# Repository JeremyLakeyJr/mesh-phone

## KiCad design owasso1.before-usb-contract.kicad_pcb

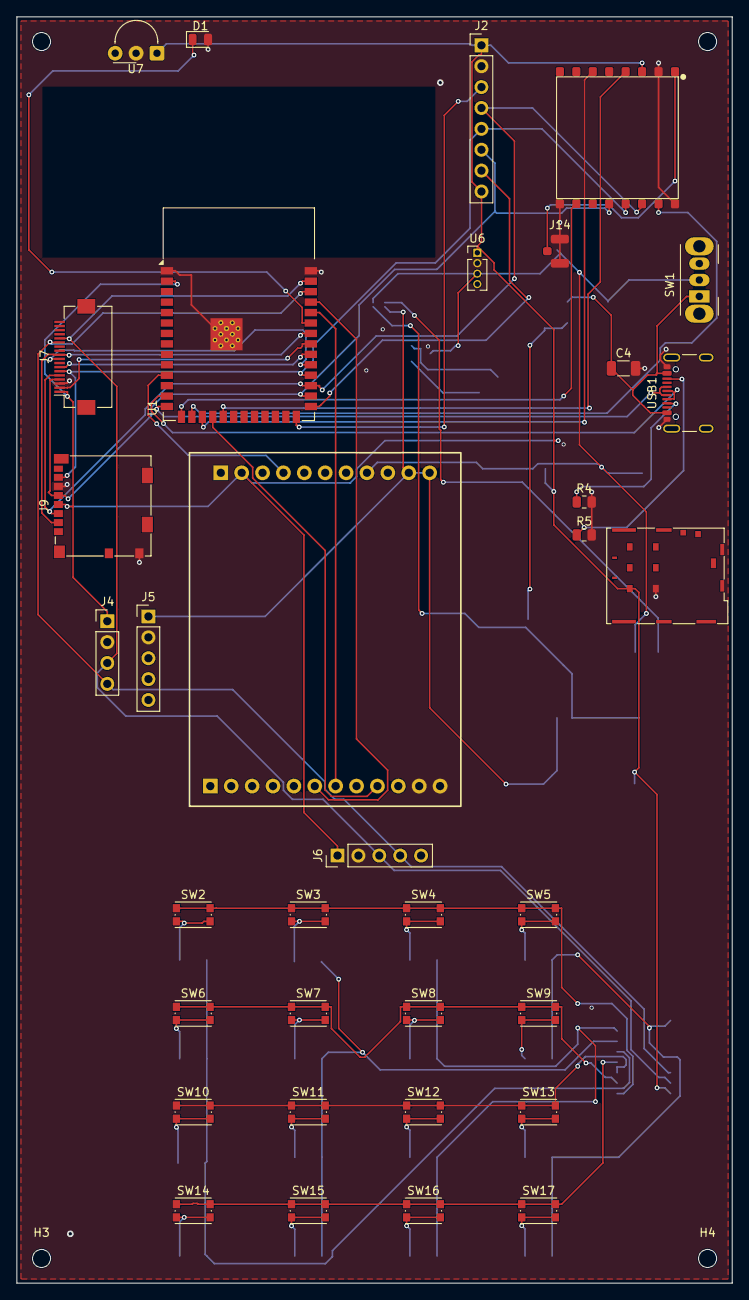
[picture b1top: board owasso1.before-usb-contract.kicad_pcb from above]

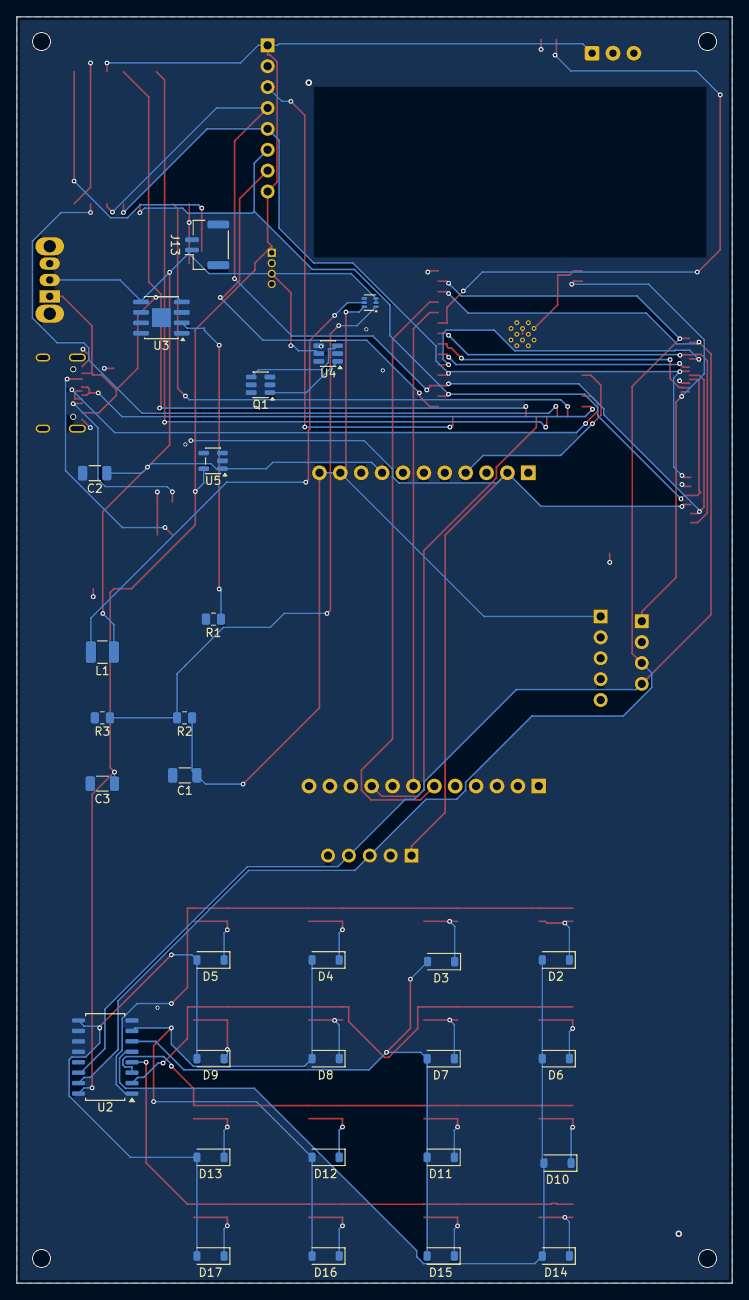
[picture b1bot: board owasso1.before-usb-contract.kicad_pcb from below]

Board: 2 copper layers, 87.0 x 154.0 mm, 69 parts (31 on the bottom side), 59 nets.

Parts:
C1: 1000uF-MODEM-BULK; C_1206_3216Metric
C2: 100uF-VBAT-BULK; C_1206_3216Metric
C3: 10uF-3V3-BULK; C_1206_3216Metric
C4: 10uF-USB-IN; C_1206_3216Metric
D1: TSAL6200-IR-LED; LED_0805_2012Metric
D2: 1N4148W-KEY-1; D_SOD-123
D3: 1N4148W-KEY-2; D_SOD-123
D4: 1N4148W-KEY-3; D_SOD-123
D5: 1N4148W-KEY-4; D_SOD-123
D6: 1N4148W-KEY-5; D_SOD-123
D7: 1N4148W-KEY-6; D_SOD-123
D8: 1N4148W-KEY-7; D_SOD-123
D9: 1N4148W-KEY-8; D_SOD-123
D10: 1N4148W-KEY-9; D_SOD-123
D11: 1N4148W-KEY-10; D_SOD-123
D12: 1N4148W-KEY-11; D_SOD-123
D13: 1N4148W-KEY-12; D_SOD-123
D14: 1N4148W-KEY-13; D_SOD-123
D15: 1N4148W-KEY-14; D_SOD-123
D16: 1N4148W-KEY-15; D_SOD-123
D17: 1N4148W-KEY-16; D_SOD-123
H1, H2, H3, H4: MountingHole_2.2mm_M2
J1: A7670E-LASE-23P-12+11; A7670E_LASE_23P_12+11
J2: CC1101-module; PinHeader_1x08_P2.54mm_Vertical
J3: Ra-01SH-SX1262-915MHz; Ra-01SH
J4: PN532-NFC-module; PinHeader_1x04_P2.54mm_Vertical
J5: RDM6300-RFID-module; PinHeader_1x05_P2.54mm_Vertical
J6: Pimoroni-PIM447-Trackball; PinHeader_1x05_P2.54mm_Vertical
J7: Waveshare-3.5in-18pin-FPC; Hirose_FH12-18S-0.5SH_1x18-1MP_P0.50mm_Horizontal
J9: MicroSD-SPI; microSD_HC_Molex_104031-0811
J10: Nano-SIM; JAE_SIM_Card_SF72S006
J13: LiPo-BATTERY-MICRO-JST-1.25; JST_GH_SM02B-GHS-TB_1x02-1MP_P1.25mm_Horizontal
J14: LoRa-UFL-Antenna; U.FL_Hirose_U.FL-R-SMT-1_Vertical
L1: 1uH-BOOST-INDUCTOR; L_1210_3225Metric
Q1: FS8205A-PROTECTION-FET; SOT-23-6
R1: 1.2k-TP4056-PROG; R_0805_2012Metric
R2: 180k-BOOST-FB; R_0805_2012Metric
R3: 27k-BOOST-FB; R_0805_2012Metric
R4: 5.1k-USB-C-CC1-Rd; R_0805_2012Metric
R5: 5.1k-USB-C-CC2-Rd; R_0805_2012Metric
SW1: Power-switch; SW_Slide_SPDT_Angled_CK_OS102011MA1Q
SW2: KEY-1; SW_Push_1P1T_NO_CK_KMR2
SW3: KEY-2; SW_Push_1P1T_NO_CK_KMR2
SW4: KEY-3; SW_Push_1P1T_NO_CK_KMR2
SW5: KEY-4; SW_Push_1P1T_NO_CK_KMR2
SW6: KEY-5; SW_Push_1P1T_NO_CK_KMR2
SW7: KEY-6; SW_Push_1P1T_NO_CK_KMR2
SW8: KEY-7; SW_Push_1P1T_NO_CK_KMR2
SW9: KEY-8; SW_Push_1P1T_NO_CK_KMR2
SW10: KEY-9; SW_Push_1P1T_NO_CK_KMR2
SW11: KEY-10; SW_Push_1P1T_NO_CK_KMR2
SW12: KEY-11; SW_Push_1P1T_NO_CK_KMR2
SW13: KEY-12; SW_Push_1P1T_NO_CK_KMR2
SW14: KEY-13; SW_Push_1P1T_NO_CK_KMR2
SW15: KEY-14; SW_Push_1P1T_NO_CK_KMR2
SW16: KEY-15; SW_Push_1P1T_NO_CK_KMR2
SW17: KEY-16; SW_Push_1P1T_NO_CK_KMR2
U1: ESP32-S3-WROOM-1-N16R8; ESP32-S3-WROOM-1
U2: PCF8574T-keypad-expander; SOIC-16_4.55x10.3mm_P1.27mm
U3: TP4056-charger; HSOP-8-1EP_3.9x4.9mm_P1.27mm_EP2.3x2.3mm
U4: DW01A-protection; SOT-23-6
U5: 3V3-LDO; SOT-23-5
U6: MAX17048-fuel-gauge; PinHeader_1x04_P1.27mm_Vertical
U7: TSOP38238-IR-receiver; Vishay_MINIMOLD-3Pin
U8: TPS61023DRLR-5V-BOOST; SOT-563
USB1: USB-C-charge-and-data; USB_C_Receptacle_GCT_USB4105-xx-A_16P_TopMnt_Horizontal

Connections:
/3V3: C3.1, J1.14, J2.1, J2.8, J3.3, J4.1, J6.1, J7.1, J9.4, J10.1, U1.2, U2.16, U5.5, U6.1, U7.1
/BOOST_FB: R2.2, R3.1, U8.1
/BOOST_SW: L1.2, U8.5
/CC1101_CS: J2.3, U1.26
/CC1101_GDO0: J2.7, U1.27
/DW01A_OC: Q1.4, U4.3
/DW01A_OD: Q1.1, U4.1
/GND: C1.2, C2.2, C3.2, C4.2, D1.2, J1.11, J1.12, J2.2, J3.2, J3.9, J3.16, J4.2, J5.2, J6.2, J7.3, J9.6, J9.10, J10.2, J13.2, J14.2, Q1.2, Q1.3, Q1.5, Q1.6, R1.2, R3.2, R4.2, R5.2, U1.1, U1.40, U1.41, U2.8, U2.10, U2.11, U2.12, U3.3, U3.9, U4.2, U4.4, U4.6, U5.2, U6.2, U7.2, U8.4, USB1.A1, USB1.A12, USB1.B1, USB1.B12
/I2C_SCL: J4.4, J6.4, J7.13, U1.38, U2.14
/I2C_SDA: J4.3, J6.3, J7.14, U1.39, U2.15
/IR_TX: D1.1, U1.35
/KEY_C1: D2.2, D6.2, D10.2, D14.2, U2.5
/KEY_C2: D3.2, D7.2, D11.2, D15.2, U2.6
/KEY_C3: D4.2, D8.2, D12.2, D16.2, U2.7
/KEY_C4: D5.2, D9.2, D13.2, D17.2, U2.9
/KEY_D1: D2.1, SW2.2
/KEY_D2: D3.1, SW3.2
/KEY_D3: D4.1, SW4.2
/KEY_D4: D5.1, SW5.2
/KEY_D5: D6.1, SW6.2
/KEY_D6: D7.1, SW7.2
/KEY_D7: D8.1, SW8.2
/KEY_D8: D9.1, SW9.2
/KEY_D9: D10.1, SW10.2
/KEY_D10: D11.1, SW11.2
/KEY_D11: D12.1, SW12.2
/KEY_D12: D13.1, SW13.2
/KEY_D13: D14.1, SW14.2
/KEY_D14: D15.1, SW15.2
/KEY_D15: D16.1, SW16.2
/KEY_D16: D17.1, SW17.2
/KEY_R1: SW2.1, SW3.1, SW4.1, SW5.1, U2.1
/KEY_R2: SW6.1, SW7.1, SW8.1, SW9.1, U2.2
/KEY_R3: SW10.1, SW11.1, SW12.1, SW13.1, U2.3
/KEY_R4: SW14.1, SW15.1, SW16.1, SW17.1, U2.4
/LCD_BL: J7.2, U1.33
/LCD_CS: J7.9, U1.31
/LCD_DC: J7.7, U1.32
/LORA_ANT: J3.1, J14.1
/LTE_PWRKEY: J1.9, U1.18
/LTE_RI: J1.16, U1.11
/LTE_RX: J1.7, U1.36
/LTE_TX: J1.6, U1.37
/MODEM_5V: C1.1, J1.22, J1.23, J5.1, R2.1, U8.6
/SD_CS: J7.10, J9.2, U1.34
/SPI_MISO: J2.5, J3.13, J7.6, J9.7, U1.30
/SPI_MOSI: J2.4, J3.14, J7.5, J9.3, U1.29
/SPI_SCK: J2.6, J3.12, J7.4, J9.5, U1.28
/SX1262_BUSY: J3.10, U1.15
/SX1262_CS: J3.15, U1.16
/SX1262_DIO1: J3.6, U1.17
/SX1262_RESET: J3.4, U1.19
/U3_PROG: R1.1, U3.2
/USB_CC1: R4.1, USB1.A5
/USB_CC2: R5.1, USB1.B5
/USB_D+: U1.14, USB1.A6, USB1.B6
/USB_D-: U1.13, USB1.A7, USB1.B7
/VBAT: C2.1, J1.20, J13.1, L1.1, SW1.2, U3.5, U4.5, U5.1, U6.3, U8.2, U8.3
/VBUS5V: C4.1, SW1.1, U3.4, USB1.A4, USB1.A9, USB1.B4, USB1.B9
